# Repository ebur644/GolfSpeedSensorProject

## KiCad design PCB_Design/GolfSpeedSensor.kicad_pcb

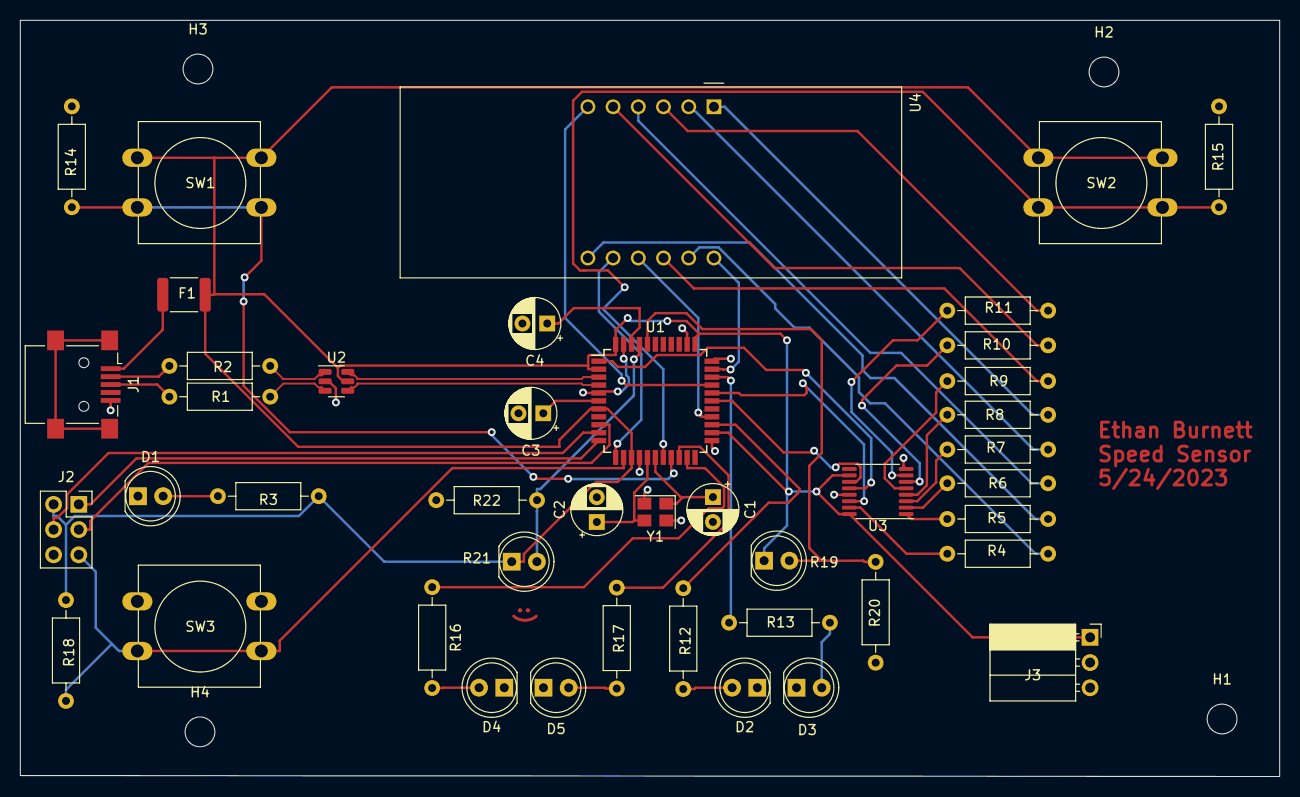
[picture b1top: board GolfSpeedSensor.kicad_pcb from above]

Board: 2 copper layers, 126.9 x 76.2 mm, 47 parts (0 on the bottom side), 53 nets.

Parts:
C1, C2: 22pF; CP_Radial_D5.0mm_P2.50mm
C3: 1uF; CP_Radial_D5.0mm_P2.50mm
C4: .1uF; CP_Radial_D5.0mm_P2.50mm
D1, D2, D3, D4, D5: LED; LED_D5.0mm_Clear
F1: PTCSMP; Fuse_1812_4532Metric
H1, H2, H3, H4: MountingHole; MountingHole_3mm
J1: USB_B_Mini; USB_Mini-B_Lumberg_2486_01_Horizontal
J2: AVR-ISP-6; PinSocket_2x03_P2.54mm_Vertical
J3: Conn_01x03_Socket; PinSocket_1x03_P2.54mm_Horizontal
R1, R2, R3: 1k; R_Axial_DIN0207_L6.3mm_D2.5mm_P10.16mm_Horizontal
R4, R5, R6, R7, R8, R9, R10, R11: 100; R_Axial_DIN0207_L6.3mm_D2.5mm_P10.16mm_Horizontal
R12, R13, R16, R17: 330; R_Axial_DIN0207_L6.3mm_D2.5mm_P10.16mm_Horizontal
R14, R15, R18, R20, R22: 10k; R_Axial_DIN0207_L6.3mm_D2.5mm_P10.16mm_Horizontal
R19, R21: R_Photo; LED_D5.0mm_Clear
SW1, SW2, SW3: SW_Push; SW_PUSH-12mm
U1: ATmega32U4-A; TQFP-44_10x10mm_P0.8mm
U2: USBLC6-2SC6; SOT-23-6
U3: 74HC595; TSSOP-16_4.4x5mm_P0.65mm
U4: CA56-12EWA
Y1: 16kHz; Crystal_SMD_Abracon_ABM8G-4Pin_3.2x2.5mm

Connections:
+5V: F1.2, J2.2 (VCC), J3.1, R3.1, R18.1, R19.1, R21.1, SW1.1, SW2.1, U1.2 (UVCC), U1.7 (VBUS), U1.14 (VCC), U1.24 (AVCC), U1.34 (VCC), U1.44 (AVCC), U2.5 (VBUS), U3.10 (~SRCLR), U3.16 (VCC)
/AREF: C4.1, U1.42 (AREF)
/UCAP: C3.1, U1.6 (UCAP)
Beam_1: R19.2, R20.2, U1.40 (PF1)
Beam_2: R21.2, R22.2, U1.41 (PF0)
Button_1: R14.1, SW1.2, U1.19 (PD1)
Button_2: R15.1, SW2.2, U1.18 (PD0)
DS: U1.29 (PB5), U3.14 (SER)
Dig1: U1.32 (PC7), U4.12 (CA1)
Dig2: U1.26 (PD6), U4.9 (CA2)
Dig3: U1.12 (PB7), U4.8 (CA3)
Dig4: U1.30 (PB6), U4.6 (CA4)
GND: C1.2, C2.2, C3.2, C4.2, D1.1 (K), D2.1 (K), D3.1 (K), D4.1 (K), D5.1 (K), J1.5 (GND), J2.6 (GND), J3.2, R14.2, R15.2, R20.1, R22.1, SW3.1, U1.5 (UGND), U1.15 (GND), U1.23 (GND), U1.33 (~HWB/PE2), U1.35 (GND), U1.43 (GND), U2.2 (GND), U3.8 (GND), U3.13 (~OE), Y1.2, Y1.4
Green_LED1: R12.1, U1.25 (PD4)
Green_LED2: R16.1, U1.21 (PD3)
MISO: J2.1 (MISO), U1.11 (PB3)
MOSI: J2.4 (MOSI), U1.10 (PB2)
unnamed: D1.2 (A), R3.2
unnamed: D2.2 (A), R12.2
unnamed: D3.2 (A), R13.2
unnamed: D4.2 (A), R16.2
unnamed: D5.2 (A), R17.2
unnamed: J1.3 (D+), R1.1
unnamed: J1.2 (D-), R2.1
unnamed: F1.1, J1.1 (VBUS)
unnamed: R11.2, U4.3 (DPX)
unnamed: R4.2, U4.11 (a)
unnamed: R5.2, U4.7 (b)
unnamed: R6.2, U4.4 (c)
unnamed: R7.2, U4.2 (d)
unnamed: R8.2, U4.1 (e)
unnamed: R9.2, U4.10 (f)
unnamed: R10.2, U4.5 (g)
RST: J2.5 (~RST), R18.2, SW3.2, U1.13 (~RESET)
Red_LED1: R13.1, U1.31 (PC6)
Red_LED2: R17.1, U1.20 (PD2)
SCK: J2.3 (SCK), U1.9 (PB1)
SH_CP: U1.28 (PB4), U3.11 (SRCLK)
ST_CP: U1.1 (PE6), U3.12 (RCLK)
USB_CONN_D+: R1.2, U2.3 (I/O2)
USB_CONN_D-: R2.2, U2.1 (I/O1)
USB_D+: U1.4 (D+), U2.4 (I/O2)
USB_D-: U1.3 (D-), U2.6 (I/O1)
XTAL1: C1.1, U1.17 (XTAL1), Y1.1
XTAL2: C2.1, U1.16 (XTAL2), Y1.3
a: R4.1, U3.15 (QA)
b: R5.1, U3.1 (QB)
c: R6.1, U3.2 (QC)
d: R7.1, U3.3 (QD)
dp: R11.1, U3.7 (QH)
e: R8.1, U3.4 (QE)
f: R9.1, U3.5 (QF)
g: R10.1, U3.6 (QG)

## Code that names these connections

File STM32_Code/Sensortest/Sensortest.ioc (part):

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Mcu.Name=STM32F407V(E-G)Tx
Mcu.Package=LQFP100
Mcu.UserName=STM32F407VGTx
PA0-WKUP.GPIOParameters=GPIO_PuPd,GPIO_Label,GPIO_ModeDefaultEXTI
PA0-WKUP.GPIO_Label=B1 [Blue PushButton]
PA0-WKUP.GPIO_ModeDefaultEXTI=GPIO_MODE_IT_RISING
PA0-WKUP.GPIO_PuPd=GPIO_NOPULL
PA0-WKUP.Signal=GPXTI0
PA10.GPIOParameters=GPIO_Speed,GPIO_PuPd,GPIO_Label,GPIO_Mode
PA10.GPIO_Label=OTG_FS_ID
PA10.GPIO_Mode=GPIO_MODE_AF_PP
PA10.GPIO_PuPd=GPIO_NOPULL
PA10.GPIO_Speed=GPIO_SPEED_FREQ_LOW
PA10.Signal=USB_OTG_FS_ID
PA11.GPIOParameters=GPIO_Speed,GPIO_PuPd,GPIO_Label,GPIO_Mode
PA11.GPIO_Label=OTG_FS_DM
PA11.GPIO_Mode=GPIO_MODE_AF_PP
PA11.GPIO_PuPd=GPIO_NOPULL
PA11.GPIO_Speed=GPIO_SPEED_FREQ_LOW
PA11.Signal=USB_OTG_FS_DM
PA12.GPIOParameters=GPIO_Speed,GPIO_PuPd,GPIO_Label,GPIO_Mode
PA12.GPIO_Label=OTG_FS_DP
PA12.GPIO_Mode=GPIO_MODE_AF_PP
PA12.GPIO_PuPd=GPIO_NOPULL
PA12.GPIO_Speed=GPIO_SPEED_FREQ_LOW
PA12.Signal=USB_OTG_FS_DP
PA13.GPIOParameters=GPIO_Label
PA13.GPIO_Label=SWDIO
PA13.Mode=Serial_Wire
PA13.Signal=SYS_JTMS-SWDIO
PA14.GPIOParameters=GPIO_Label
PA14.GPIO_Label=SWCLK
PA14.Mode=Serial_Wire
PA14.Signal=SYS_JTCK-SWCLK
PA4.GPIOParameters=GPIO_Speed,GPIO_PuPd,GPIO_Label,GPIO_Mode
PA4.GPIO_Label=I2S3_WS [CS43L22_LRCK]
PA4.GPIO_Mode=GPIO_MODE_AF_PP
PA4.GPIO_PuPd=GPIO_NOPULL
PA4.GPIO_Speed=GPIO_SPEED_FREQ_LOW
PA4.Signal=I2S3_WS
PA5.GPIOParameters=GPIO_Speed,GPIO_PuPd,GPIO_Label,GPIO_Mode
PA5.GPIO_Label=SPI1_SCK [LIS302DL_SCL/SPC]
PA5.GPIO_Mode=GPIO_MODE_AF_PP
PA5.GPIO_PuPd=GPIO_NOPULL
PA5.GPIO_Speed=GPIO_SPEED_FREQ_LOW
PA5.Signal=SPI1_SCK
PA6.GPIOParameters=GPIO_Speed,GPIO_PuPd,GPIO_Label,GPIO_Mode
PA6.GPIO_Label=SPI1_MISO [LIS302DL_SDO]
PA6.GPIO_Mode=GPIO_MODE_AF_PP
PA6.GPIO_PuPd=GPIO_NOPULL
PA6.GPIO_Speed=GPIO_SPEED_FREQ_LOW
PA6.Signal=SPI1_MISO
PA7.GPIOParameters=GPIO_Speed,GPIO_PuPd,GPIO_Label,GPIO_Mode
PA7.GPIO_Label=SPI1_MOSI [LIS302DL_SDA/SDI/SDO]
PA7.GPIO_Mode=GPIO_MODE_AF_PP
PA7.GPIO_PuPd=GPIO_NOPULL
PA7.GPIO_Speed=GPIO_SPEED_FREQ_LOW
PA7.Signal=SPI1_MOSI
PA9.GPIOParameters=GPIO_PuPd,GPIO_Label,GPIO_Mode
PA9.GPIO_Label=VBUS_FS
PA9.GPIO_Mode=GPIO_MODE_INPUT
PA9.GPIO_PuPd=GPIO_NOPULL
PA9.Signal=USB_OTG_FS_VBUS
PB0.GPIOParameters=GPIO_Label
PB0.GPIO_Label=BOOT1
PB0.Signal=GPIO_Input
PB10.GPIOParameters=GPIO_Speed,GPIO_PuPd,GPIO_Label,GPIO_Mode
PB10.GPIO_Label=CLK_IN [MP45DT02_CLK]
PB10.GPIO_Mode=GPIO_MODE_AF_PP
PB10.GPIO_PuPd=GPIO_NOPULL
PB10.GPIO_Speed=GPIO_SPEED_FREQ_LOW
PB10.Signal=I2S2_CK
PB13.GPIOParameters=GPIO_Label
PB13.GPIO_Label=RED_LED2
PB13.Signal=GPIO_Output
PB14.GPIOParameters=GPIO_Label
PB14.GPIO_Label=GREEN_LED2
PB14.Signal=GPIO_Output
PB15.GPIOParameters=GPIO_Label
PB15.GPIO_Label=RED_LED1
PB15.Signal=GPIO_Output
PB3.GPIOParameters=GPIO_Label
PB3.GPIO_Label=SWO
PB3.Signal=SYS_JTDO-SWO
PB6.GPIOParameters=GPIO_Speed,GPIO_PuPd,GPIO_Label,GPIO_Pu,GPIO_Mode
PB6.GPIO_Label=Audio_SCL [CS43L22_SCL]
PB6.GPIO_Mode=GPIO_MODE_AF_OD
PB6.GPIO_Pu=GPIO_PULLUP
PB6.GPIO_PuPd=GPIO_NOPULL
PB6.GPIO_Speed=GPIO_SPEED_FREQ_LOW
PB6.Signal=I2C1_SCL
PB9.GPIOParameters=GPIO_Speed,GPIO_PuPd,GPIO_Label,GPIO_Pu,GPIO_Mode
PB9.GPIO_Label=Audio_SDA [CS43L22_SDA]
PB9.GPIO_Mode=GPIO_MODE_AF_OD
PB9.GPIO_Pu=GPIO_PULLUP
PB9.GPIO_PuPd=GPIO_NOPULL
PB9.GPIO_Speed=GPIO_SPEED_FREQ_LOW
PB9.Signal=I2C1_SDA
PC0.GPIOParameters=GPIO_Speed,PinState,GPIO_PuPd,GPIO_Label
PC0.GPIO_Label=OTG_FS_PowerSwitchOn
PC0.GPIO_PuPd=GPIO_NOPULL
PC0.GPIO_Speed=GPIO_SPEED_FREQ_LOW
PC0.PinState=GPIO_PIN_SET
PC0.Signal=GPIO_Output
PC10.GPIOParameters=GPIO_Speed,GPIO_PuPd,GPIO_Label,GPIO_Mode
PC10.GPIO_Label=I2S3_SCK [CS43L22_SCLK]
PC10.GPIO_Mode=GPIO_MODE_AF_PP
PC10.GPIO_PuPd=GPIO_NOPULL
PC10.GPIO_Speed=GPIO_SPEED_FREQ_LOW
PC10.Signal=I2S3_CK
PC12.GPIOParameters=GPIO_Speed,GPIO_PuPd,GPIO_Label,GPIO_Mode
PC12.GPIO_Label=I2S3_SD [CS43L22_SDIN]
PC12.GPIO_Mode=GPIO_MODE_AF_PP
PC12.GPIO_PuPd=GPIO_NOPULL
PC12.GPIO_Speed=GPIO_SPEED_FREQ_LOW
PC12.Signal=I2S3_SD
PC14-OSC32_IN.GPIOParameters=GPIO_Label
PC14-OSC32_IN.GPIO_Label=PC14-OSC32_IN
PC14-OSC32_IN.Mode=LSE-External-Oscillator
PC14-OSC32_IN.Signal=RCC_OSC32_IN
PC15-OSC32_OUT.GPIOParameters=GPIO_Label
PC15-OSC32_OUT.GPIO_Label=PC15-OSC32_OUT
PC15-OSC32_OUT.Mode=LSE-External-Oscillator
PC15-OSC32_OUT.Signal=RCC_OSC32_OUT
PC3.GPIOParameters=GPIO_Speed,GPIO_PuPd,GPIO_Label,GPIO_Mode
PC3.GPIO_Label=PDM_OUT [MP45DT02_DOUT]
PC3.GPIO_Mode=GPIO_MODE_AF_PP
PC3.GPIO_PuPd=GPIO_NOPULL
PC3.GPIO_Speed=GPIO_SPEED_FREQ_LOW
PC3.Signal=I2S2_SD
PC4.GPIOParameters=GPIO_Label
PC4.GPIO_Label=BUTTON_1
PC4.Signal=GPXTI4
PC5.GPIOParameters=GPIO_Label
PC5.GPIO_Label=BUTTON_2
PC5.Signal=GPXTI5
PC7.GPIOParameters=GPIO_Speed,GPIO_PuPd,GPIO_Label,GPIO_Mode
PC7.GPIO_Label=I2S3_MCK [CS43L22_MCLK]
PC7.GPIO_Mode=GPIO_MODE_AF_PP
PC7.GPIO_PuPd=GPIO_NOPULL
PC7.GPIO_Speed=GPIO_SPEED_FREQ_LOW
PC7.Signal=I2S3_MCK
PD10.GPIOParameters=GPIO_Label
PD10.GPIO_Label=LDR2
PD10.Signal=GPXTI10
PD11.GPIOParameters=GPIO_Label
PD11.GPIO_Label=LDR1
PD11.Signal=GPXTI11
PD4.GPIOParameters=GPIO_Speed,GPIO_PuPd,GPIO_Label
PD4.GPIO_Label=Audio_RST [CS43L22_RESET]
PD4.GPIO_PuPd=GPIO_NOPULL
PD4.GPIO_Speed=GPIO_SPEED_FREQ_LOW
PD4.Signal=GPIO_Output
PD5.GPIOParameters=GPIO_PuPd,GPIO_Label,GPIO_Mode
PD5.GPIO_Label=OTG_FS_OverCurrent
PD5.GPIO_Mode=GPIO_MODE_INPUT
PD5.GPIO_PuPd=GPIO_NOPULL
PD5.Signal=GPIO_Input
PD8.GPIOParameters=GPIO_Label
PD8.GPIO_Label=GREEN_LED1
PD8.Signal=GPIO_Input
PD9.GPIOParameters=GPIO_Label
PD9.GPIO_Label=LEDRESET
PD9.Signal=GPIO_Input
PE1.GPIOParameters=GPIO_PuPd,GPIO_Label,GPIO_ModeDefaultEXTI
PE1.GPIO_Label=MEMS_INT2 [LIS302DL_INT2]
PE1.GPIO_ModeDefaultEXTI=GPIO_MODE_EVT_RISING
PE1.GPIO_PuPd=GPIO_NOPULL
PE1.Signal=GPXTI1
PE10.GPIOParameters=GPIO_Label
PE10.GPIO_Label=DIGIT4
PE10.Signal=GPIO_Output
PE11.GPIOParameters=GPIO_Label
PE11.GPIO_Label=CLOCK
PE11.Signal=GPIO_Output
PE12.GPIOParameters=GPIO_Label
PE12.GPIO_Label=LATCH
PE12.Signal=GPIO_Output
PE13.GPIOParameters=GPIO_Label
PE13.GPIO_Label=DATA
PE13.Signal=GPIO_Output
PE3.GPIOParameters=GPIO_Speed,GPIO_PuPd,GPIO_Label
PE3.GPIO_Label=CS_I2C/SPI [LIS302DL_CS_I2C/SPI]
PE3.GPIO_PuPd=GPIO_NOPULL
PE3.GPIO_Speed=GPIO_SPEED_FREQ_LOW
PE3.Signal=GPIO_Output
PE7.GPIOParameters=GPIO_Label
PE7.GPIO_Label=DIGIT1
PE7.Signal=GPIO_Output
PE8.GPIOParameters=GPIO_Label
PE8.GPIO_Label=DIGIT2
PE8.Signal=GPIO_Output
PE9.GPIOParameters=GPIO_Label
PE9.GPIO_Label=DIGIT3
PE9.Signal=GPIO_Output
PH0-OSC_IN.GPIOParameters=GPIO_Label
PH0-OSC_IN.GPIO_Label=PH0-OSC_IN
PH0-OSC_IN.Mode=HSE-External-Oscillator
PH0-OSC_IN.Signal=RCC_OSC_IN
PH1-OSC_OUT.GPIOParameters=GPIO_Label
PH1-OSC_OUT.GPIO_Label=PH1-OSC_OUT
PH1-OSC_OUT.Mode=HSE-External-Oscillator
PH1-OSC_OUT.Signal=RCC_OSC_OUT
RCC.HSE_VALUE=8000000
RCC.SYSCLKFreq_VALUE=168000000
RCC.SYSCLKSource=RCC_SYSCLKSOURCE_PLLCLK
board=STM32F407G-DISC1
boardIOC=true

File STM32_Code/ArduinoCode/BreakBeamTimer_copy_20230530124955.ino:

#define LDR1 2
#define LDR2 3

#define DATA 9   // DS
#define LATCH 8  // ST_CP
#define CLOCK 7  // SH_CP

#define DIGIT_4 10
#define DIGIT_3 11
#define DIGIT_2 12
#define DIGIT_1 13

#define GREEN_LED1 5
#define RED_LED1 6
#define GREEN_LED2 7
#define RED_LED2 4

// 7-Seg Display Variables
unsigned char gTable[] = { 0x3f, 0x06, 0x5b, 0x4f, 0x66, 0x6d, 0x7d, 0x07, 0x7f, 0x6f, 0x77, 0x7c, 0x39, 0x5e, 0x79, 0x71, 0x00 };


float gstartTime = 0;
float Time = 0;
unsigned long gSpeed = 0;

volatile bool gLDR1_ISR_Flag = 0;
volatile bool gLDR2_ISR_Flag = 0;

bool startFlag = 0;
double gDist = 1.5;

volatile bool gbutton1_ISR_Flag = 0;
volatile bool gbutton2_ISR_Flag = 0;

byte gCurrentDigit;

unsigned int gReloadTimer1 = 62500;
byte gReloadTimer2 = 10;  


void setup() {

  Serial.begin(9600);
  // put your setup code here, to run once
  pinMode(LDR1, INPUT_PULLUP);
  attachInterrupt(digitalPinToInterrupt(LDR1), LDR1_ISR, FALLING);

  pinMode(LDR2, INPUT_PULLUP);
  attachInterrupt(digitalPinToInterrupt(LDR2), LDR2_ISR, FALLING);

  pinMode(GREEN_LED1, OUTPUT);
  pinMode(RED_LED1, OUTPUT);
  pinMode(GREEN_LED2, OUTPUT);
  pinMode(RED_LED2, OUTPUT);

  pinMode(DIGIT_1, OUTPUT);
  pinMode(DIGIT_2, OUTPUT);
  pinMode(DIGIT_3, OUTPUT);
  pinMode(DIGIT_4, OUTPUT);

  // Shift Register Pins
  pinMode(LATCH, OUTPUT);
  pinMode(CLOCK, OUTPUT);
  pinMode(DATA, OUTPUT);


  noInterrupts();  // disable all interrupts
  TCCR2A = 0;
  TCCR2B = 0;
  TCNT2 = 0;
  OCR2A = 10;            // compare match register 16MHz/256
  TCCR2A |= (1 << WGM22);   // CTC mode
  TCCR2B = (1 << CS22)| (1<<CS21) | (1<<CS20);    // 256 prescaler
  TIMSK2 |= (1 << OCIE2A);  // enable timer compare interrupt


  TCCR1B = 0x00; // clock frequency / 1024
  //OCR2B = 0x00;  // Output compare
  TCNT1= 0;     // Set counter 2 to zero
  TIMSK1 = 0x01; // Enable overflow interrupt
  interrupts();
}



void startCheck() {
  while (digitalRead(LDR1) == HIGH && digitalRead(LDR2) == HIGH) {
    if (digitalRead(LDR1) == LOW) {
      digitalWrite(GREEN_LED1, HIGH);
    } else {
      digitalWrite(GREEN_LED1, LOW);
    }
    if (digitalRead(LDR2) == LOW) {
      digitalWrite(GREEN_LED2, HIGH);
    } else {
      digitalWrite(GREEN_LED2, LOW);
    }
  } 
}

//start button
void button1ISR() {
  // Set ISR Flag
  gbutton1_ISR_Flag = 1;
  if(digitalRead(LDR1) == HIGH && digitalRead(LDR2) == HIGH){
    startFlag = 1;
  }
  
}

//reset button (clears interupt flags and resets the)
void button2ISR() {
  // Set ISR Flag
  gbutton2_ISR_Flag = 1;

  gSpeed = 0;  

  if (gLDR1_ISR_Flag == 1) {
    gLDR1_ISR_Flag = 0;
  }
  if (gLDR2_ISR_Flag == 1) {
    gLDR2_ISR_Flag = 0;
  }
}

ISR(TIMER1_OVF_vect) {}

//ISR that switches through the digits for the 7 seg display
ISR(TIMER2_COMPA_vect)  // Timer2 interrupt service routine (ISR)
{
  dispOff();  // turn off the display

  switch (gCurrentDigit) {
    case 1:                                     //0x:xx
      display(((gSpeed / 1000)) % 10, 0);  // prepare to display digit 1 (most left)
      digitalWrite(DIGIT_1, LOW);               // turn on digit 1
      break;

    case 2:                               //x0:xx
      display((gSpeed / 100) % 10, 0);  // prepare to display digit 2
      digitalWrite(DIGIT_2, LOW);         // turn on digit 2
      break;

    case 3:                           //xx:0x
      display((gSpeed / 10) % 10, 1);  // prepare to display digit 3
      digitalWrite(DIGIT_3, LOW);     // turn on digit 3
      break;

    case 4:                        //xx:x0
      display(gSpeed % 10, 0);     // prepare to display digit 4 (most right)
      digitalWrite(DIGIT_4, LOW);  // turn on digit 4
      break;

    default:
      break;
  }

  gCurrentDigit = (gCurrentDigit % 4) + 1;
}

//Displays numbers on the 7 segmant display
void display(unsigned char num, unsigned char dp) {
  digitalWrite(LATCH, LOW);
  shiftOut(DATA, CLOCK, MSBFIRST, gTable[num] | (dp << 7));
  digitalWrite(LATCH, HIGH);
}

//turns the display off
void dispOff() {
  digitalWrite(DIGIT_1, HIGH);
  digitalWrite(DIGIT_2, HIGH);
  digitalWrite(DIGIT_3, HIGH);
  digitalWrite(DIGIT_4, HIGH);
}

//ISR for the first LDR
void LDR1_ISR() {
  // Serial.println("LDR1");
  // if (gLDR1_ISR_Flag == 0) {
  //   gLDR1_ISR_Flag = 1;
  gLDR1_ISR_Flag = 1;

    gstartTime = micros();
  }


//ISR for the second LDR 
void LDR2_ISR() {
  // Serial.println("LDR2");
  gLDR2_ISR_Flag = 0;
  if(gLDR1_ISR_Flag == 1){
    Time = micros() - gstartTime;
   gSpeed = (gDist * .000157828) / (Time * 0.00000000027778);
   Serial.print(gSpeed);
   Serial.println(" MPH");
  }
  delay(3000);
  gSpeed = 0;
  Time = 0;
  gstartTime = 0;
}

void loop() {
 //clears ISR flags


  if (gbutton1_ISR_Flag == 1) {
    gbutton1_ISR_Flag = 0;
  }
  if (gbutton2_ISR_Flag == 1) {
    gbutton2_ISR_Flag = 0;
  }
  
  //waits for sensors to be alligned and the start button to be pressed
  // while(startFlag == 0){
  //   startCheck();
  // }  
}
